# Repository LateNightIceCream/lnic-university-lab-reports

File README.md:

# lnic-university-lab-reports
lab reports, notes and code from most of my courses

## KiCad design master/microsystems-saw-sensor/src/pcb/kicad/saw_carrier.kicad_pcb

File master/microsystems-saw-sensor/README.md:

# microsystems-saw-sensor
Fabrication of a SAW (Surface Acoustic Wave) Sensor (WIP)

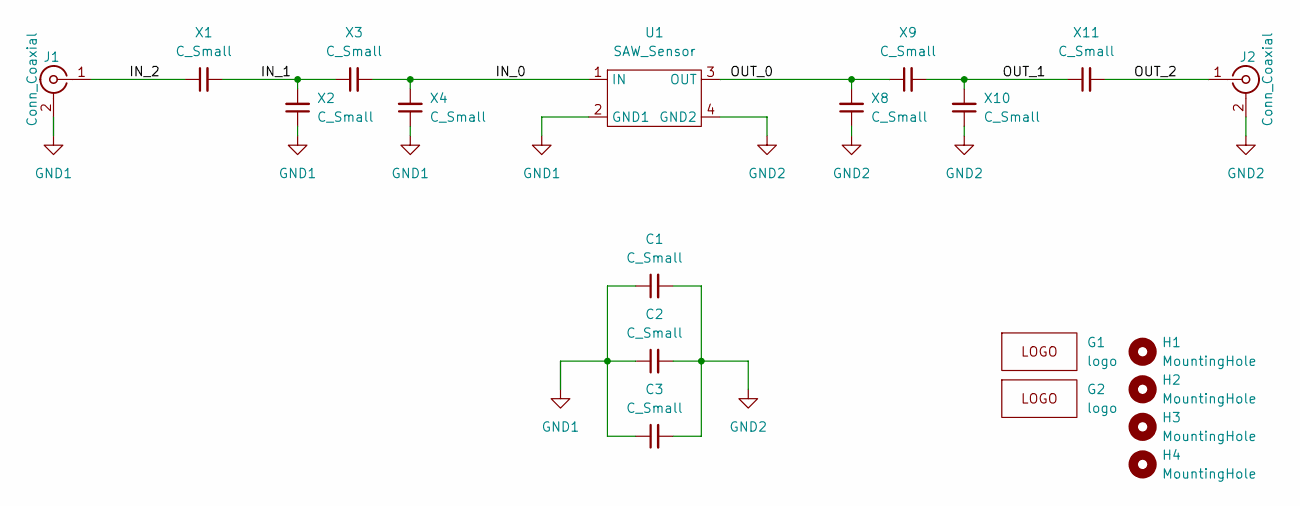
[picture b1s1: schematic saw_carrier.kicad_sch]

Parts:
C1, C2, C3: C_Small; C_0603_1608Metric
G1: logo; hs_wismar_logo_12mmx9_2mm
G2: logo; hs_wismar_logo_6_2mmx5mm
H1, H2, H3, H4: MountingHole; MountingHole_3.2mm_M3
J1, J2: Conn_Coaxial; SMA_Amphenol_132134-11_Vertical
U1: SAW_Sensor; saw_sensor
X1, X2, X3, X4, X8, X9, X10, X11: C_Small; C_0603_1608Metric

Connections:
/IN_0: U1.1 (IN), X3.2, X4.2
/IN_1: X1.2, X2.2, X3.1
/IN_2: J1.1 (In), X1.1
/OUT_0: U1.3 (OUT), X8.2, X9.1
/OUT_1: X9.2, X10.2, X11.1
/OUT_2: J2.1 (In), X11.2
GND1: C1.1, C2.1, C3.1, J1.2 (Ext), U1.2 (GND1), X2.1, X4.1
GND2: C1.2, C2.2, C3.2, J2.2 (Ext), U1.4 (GND2), X8.1, X10.1

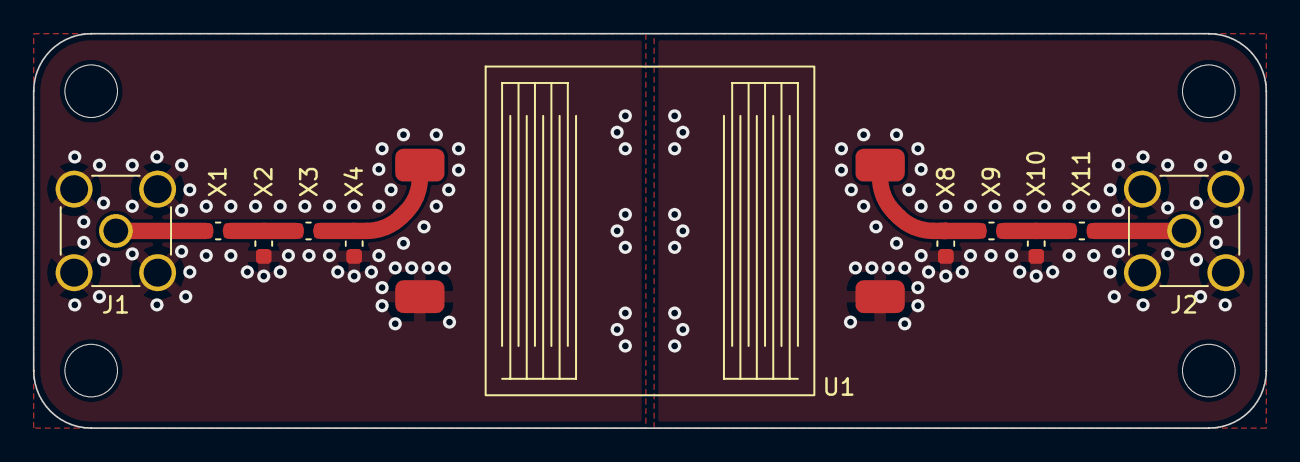
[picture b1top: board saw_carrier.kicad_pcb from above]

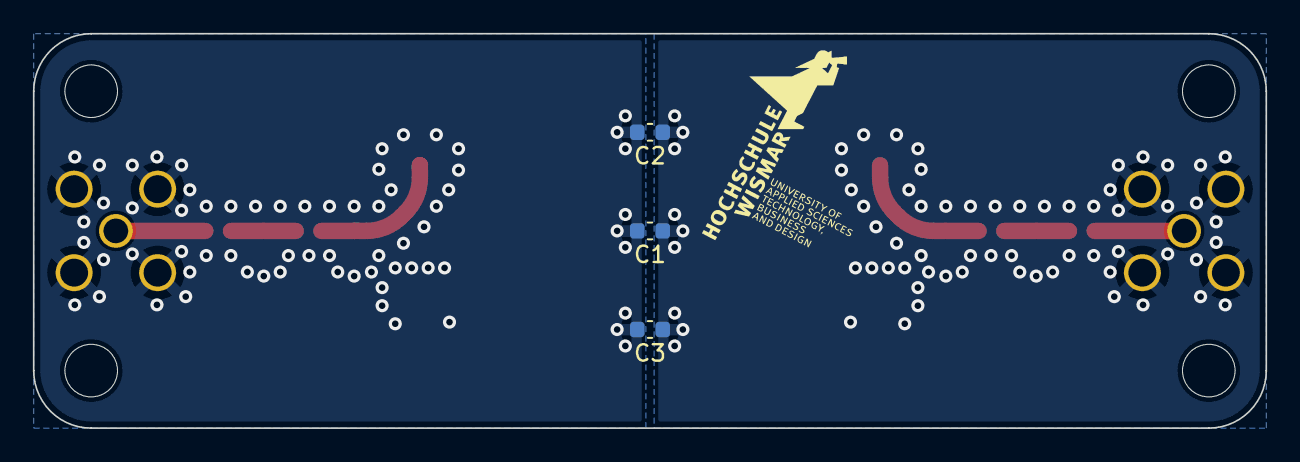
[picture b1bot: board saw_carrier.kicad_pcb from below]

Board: 2 copper layers, 75.0 x 24.0 mm, 20 parts (4 on the bottom side), 8 nets.

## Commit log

2024-04-10 added all those files!
2024-04-10 move plutosdr-project from old repo to here
2024-04-10 add mst
2024-10-16 upload PVS
